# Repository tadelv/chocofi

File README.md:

# chocofi

Keyboard shield and 3d printed case to use with Arduino ProMicro-like contoller.

- Split keyboard with 3 rows, 5 columns, and 3 thumbs per half
- Increased pinky column stagger
- Inspired by [Fifi keyboard](https://github.com/raychengy/fifi_split_keeb)
- Double-sided pcb (pcb can be used as left or right half)
- Pro Micro compatible footprint
- Easy to print, FDM-friendly two-piece case

## Artifacts

Hotswap PCB

[IBOM](https://htmlpreview.github.io/?https://github.com/krikun98/chocofi/blob/main/pcb/hotswap/bom/ibom.html)

[gerbers](../../releases/latest/download/pcb_hotswap_gerbers.zip)

front|back
--|--
|

[Plate gerbers](../../releases/latest/download/gerber_case_files.zip)

Stls are here: [case folder](/case)

For more photos check out the [pictures folder](/pictures)

## By the way

Recommended batteries:

- [Nice nano docs](https://nicekeyboards.com/docs/nice-nano/#recommended-batteries-and-sockets) explains some basics
- [nRFmicro wiki](https://github.com/joric/nrfmicro/wiki/Batteries#301230) contains links to Aliexpress

Awesome libs used:

- [kbd.pretty](https://github.com/krikun98/kbd) by foostan & krikun98
- [keyswitches.pretty](https://github.com/daprice/keyswitches.pretty) by daprice
- [Buttons_Switches.pretty](https://github.com/ElessarCuthalion/KiCAD_library/tree/master/Buttons_Switches.pretty) by ElessarCuthalion

Also closest alternatives are:

- [raychengy/fifi](https://github.com/raychengy/fifi_split_keeb): non choc (mx switches)
- [davidphilipbarr/chocorne](https://github.com/davidphilipbarr/36keys/tree/master/42Keys/chocorne): non hotswap but choc-spaced corne (you can break off one column so it will be 5x3, but with corne pinky stagger)

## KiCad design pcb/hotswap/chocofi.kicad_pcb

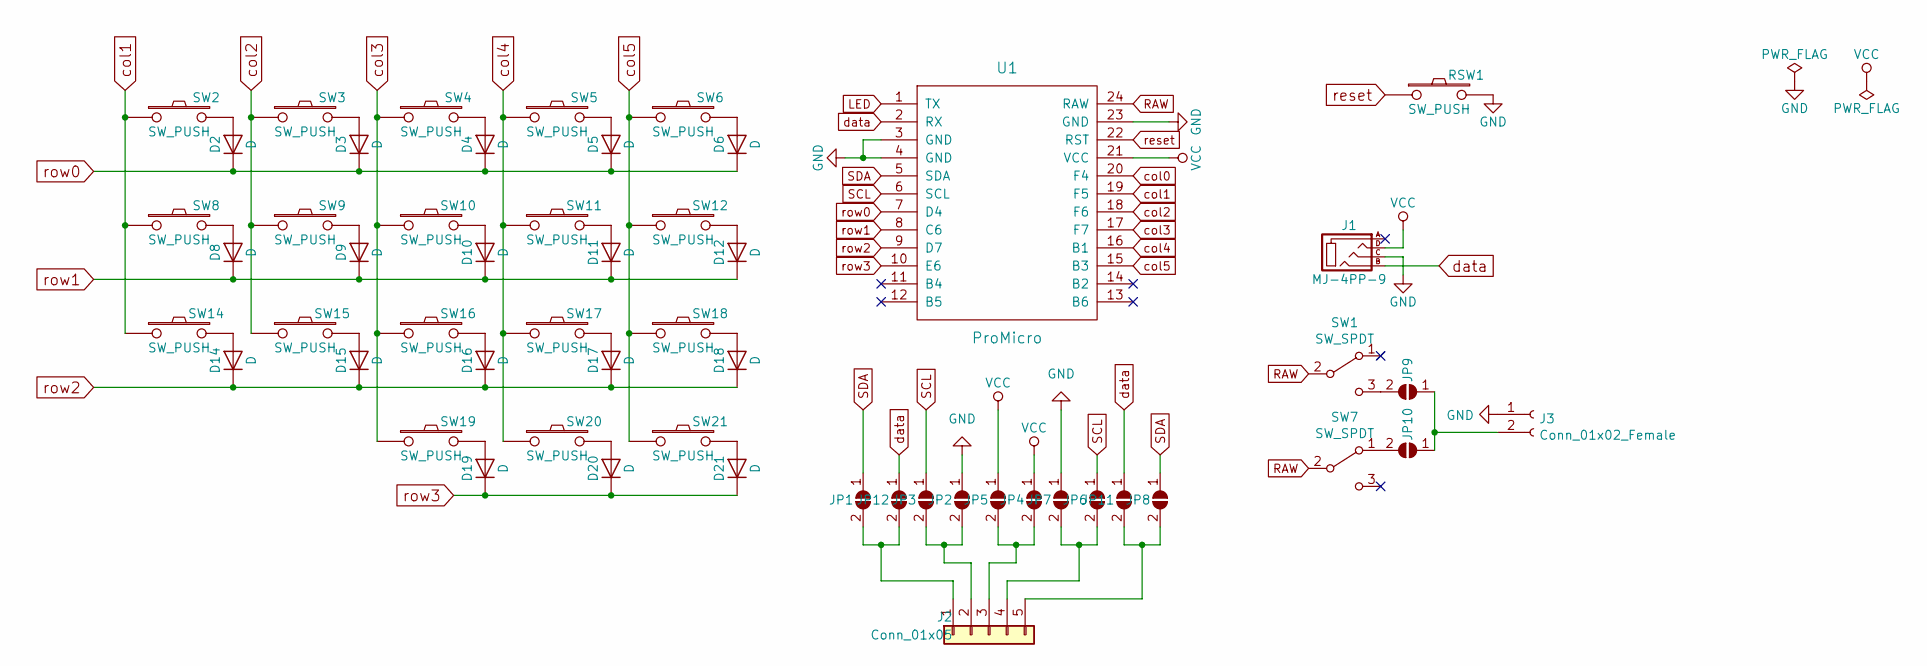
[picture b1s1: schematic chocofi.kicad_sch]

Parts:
D2, D3, D4, D5, D6, D8, D9, D10, D11, D12, D14, D15, D16, D17, D18, D19, D20, D21: D; D3_TH_SMD
J1: MJ-4PP-9
J2: Conn_01x05; nice_view_1side
J3: Conn_01x02_Female; Battery_TH
JP1, JP8: SDA; Jumper
JP2, JP7: GND; Jumper
JP3, JP6: SCL; Jumper
JP4, JP5: VCC; Jumper
JP9, JP10: SolderJumper_2_Open; Jumper
JP11, JP12: CS; Jumper
RSW1: SW_PUSH; ResetSW
SW1, SW7: SW_SPDT; SW_SPDT+H-MSK12C01_hor(7pin_SMD)
SW2, SW3, SW4, SW5, SW6, SW8, SW9, SW10, SW11, SW12, SW14, SW15, SW16, SW17, SW18, SW19, SW20, SW21: SW_PUSH; Kailh_socket_PG1350_reversible
U1: ProMicro; ProMicro_v2

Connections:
GND: J3.1, JP2.1 (A), JP7.1 (A), RSW1.2, U1.3 (GND), U1.4 (GND), U1.23 (GND)
LED: U1.1 (TX)
unnamed: D2.2 (A), SW2.2
unnamed: D3.2 (A), SW3.2
unnamed: D4.2 (A), SW4.2
unnamed: D5.2 (A), SW5.2
unnamed: D6.2 (A), SW6.2
unnamed: D8.2 (A), SW8.2
unnamed: D9.2 (A), SW9.2
unnamed: D10.2 (A), SW10.2
unnamed: D11.2 (A), SW11.2
unnamed: D12.2 (A), SW12.2
unnamed: D14.2 (A), SW14.2
unnamed: D15.2 (A), SW15.2
unnamed: D16.2 (A), SW16.2
unnamed: D17.2 (A), SW17.2
unnamed: D18.2 (A), SW18.2
unnamed: D19.2 (A), SW19.2
unnamed: D20.2 (A), SW20.2
unnamed: D21.2 (A), SW21.2
unnamed: J2.1, JP1.2 (B), JP12.2 (B)
unnamed: J2.2, JP2.2 (B), JP3.2 (B)
unnamed: J2.3, JP4.2 (B), JP5.2 (B)
unnamed: J2.4, JP6.2 (B), JP7.2 (B)
unnamed: J2.5, JP8.2 (B), JP11.2 (B)
unnamed: J3.2, JP9.1 (A), JP10.1 (A)
unnamed: JP9.2 (B), SW1.3 (C)
unnamed: JP10.2 (B), SW7.1 (A)
RAW: SW1.2 (B), SW7.2 (B), U1.24 (RAW)
SCL: JP3.1 (A), JP6.1 (A), U1.6 (SCL)
SDA: JP1.1 (A), JP8.1 (A), U1.5 (SDA)
VCC: JP4.1 (A), JP5.1 (A), U1.21 (VCC)
col0: U1.20 (F4)
col1: SW2.1, SW8.1, SW14.1, U1.19 (F5)
col2: SW3.1, SW9.1, SW15.1, U1.18 (F6)
col3: SW4.1, SW10.1, SW16.1, SW19.1, U1.17 (F7)
col4: SW5.1, SW11.1, SW17.1, SW20.1, U1.16 (B1)
col5: SW6.1, SW12.1, SW18.1, SW21.1, U1.15 (B3)
data: JP11.1 (A), JP12.1 (A), U1.2 (RX)
reset: RSW1.1, U1.22 (RST)
row0: D2.1 (K), D3.1 (K), D4.1 (K), D5.1 (K), D6.1 (K), U1.7 (D4)
row1: D8.1 (K), D9.1 (K), D10.1 (K), D11.1 (K), D12.1 (K), U1.8 (C6)
row2: D14.1 (K), D15.1 (K), D16.1 (K), D17.1 (K), D18.1 (K), U1.9 (D7)
row3: D19.1 (K), D20.1 (K), D21.1 (K), U1.10 (E6)

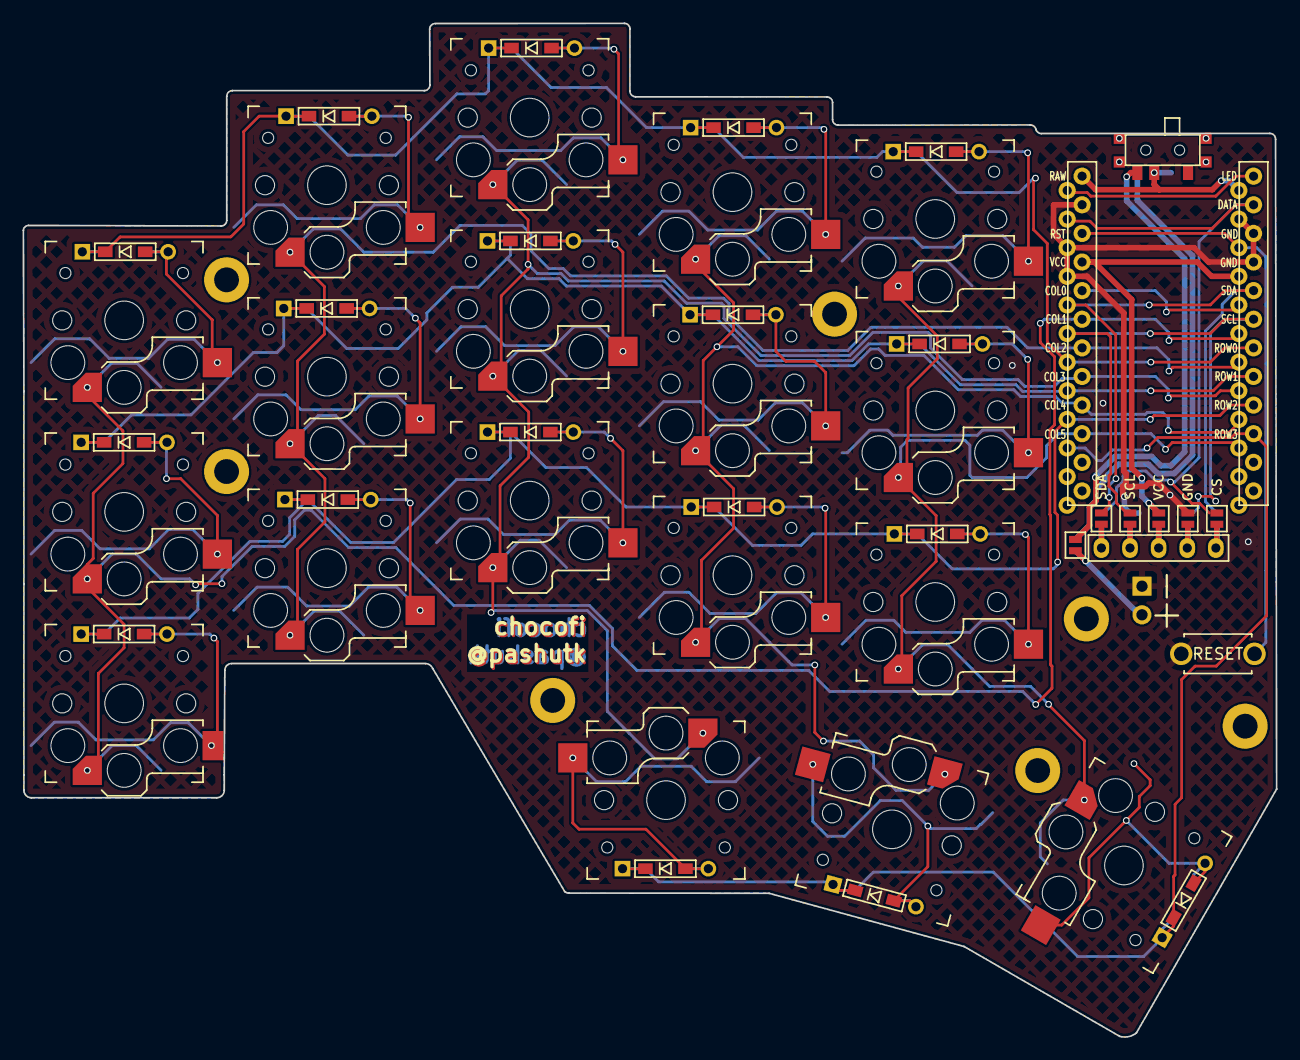
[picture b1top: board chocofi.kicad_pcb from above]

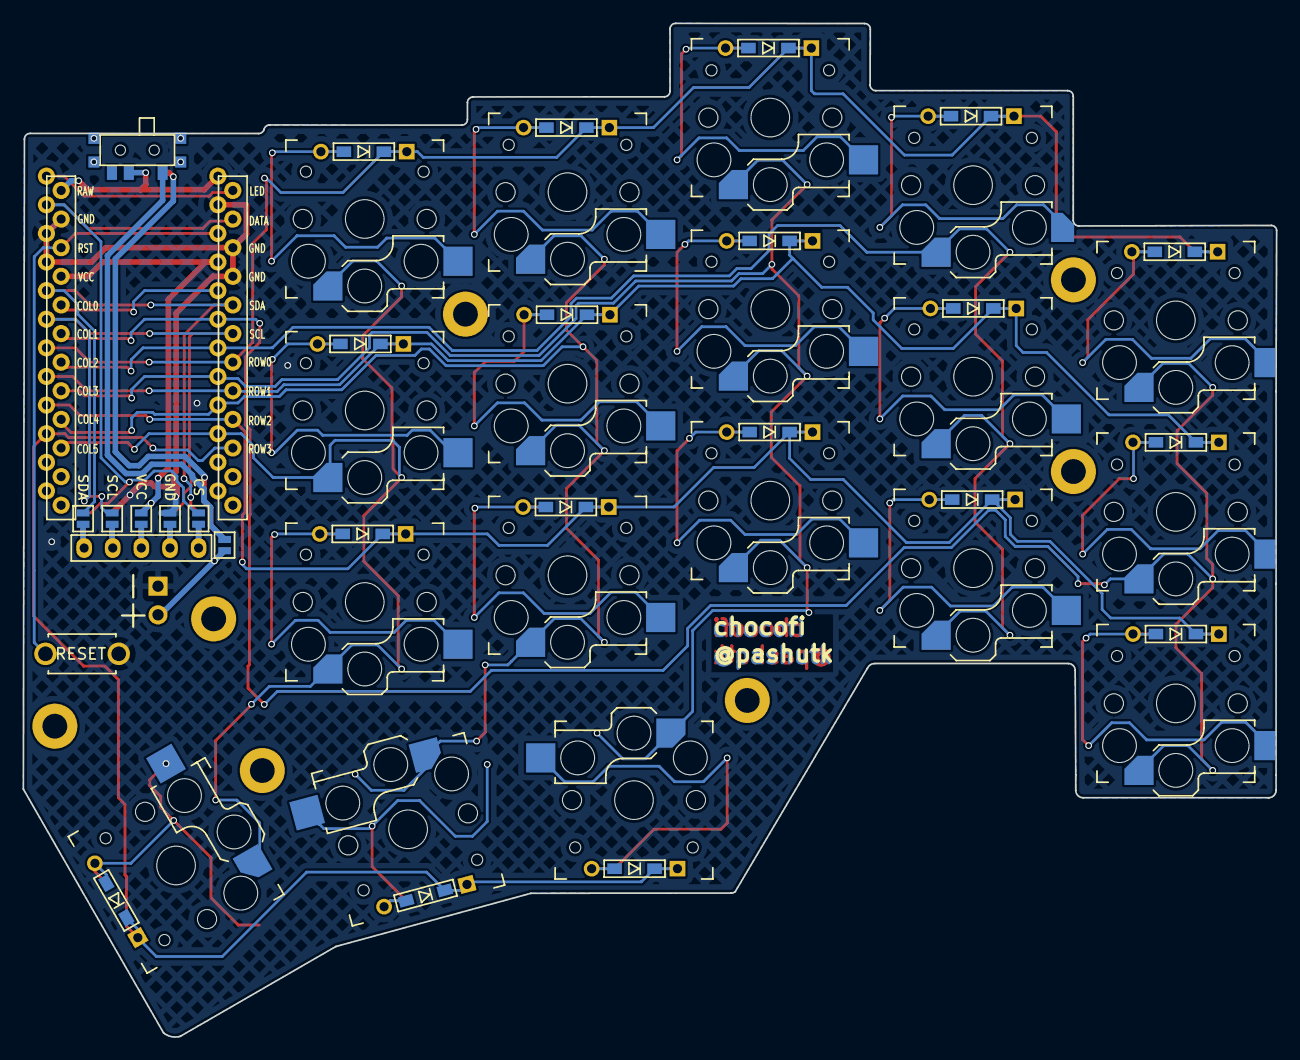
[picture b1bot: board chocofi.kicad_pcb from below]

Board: 2 copper layers, 111.3 x 90.0 mm, 61 parts (7 on the bottom side), 42 nets.

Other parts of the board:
H1: h1; LEGO_HOLE
h2: h2; LEGO_HOLE
h3: h3; LEGO_HOLE
h4: h4; LEGO_HOLE
h5: h5; LEGO_HOLE
h6: h6; LEGO_HOLE
h7: h7; LEGO_HOLE

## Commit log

2023-04-16 Added dedicated library folder
2023-04-16 Moved pictures
2023-04-16 Moved plate to dedicated directory
2023-04-16 Move pcb to nested directory
2023-04-16 Modified .gitignore
2023-04-16 Create github build pipeline
2023-04-16 Add IBOM
2023-04-16 Typo
2023-04-16 Update actions
2023-04-16 Update actions again
2023-04-17 Add niceview support, move power switch
2023-04-17 Double-sided niceview footprint
2024-11-20 move reset button
2024-11-20 Squash merge rst-button-placement into main
